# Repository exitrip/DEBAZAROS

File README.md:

<p align="center">
  
  <br>
  <sub>Robert Fludd, <i>Utriusque Cosmi Maioris … Historia</i> (1617)</sub>
</p>

> [!IMPORTANT]
> This repo contains a lot of LLM generated code as of about Aug. 15th 2026.  
> Generally this is bad for the world as much as I wanna hem and haw about
> recycling all the embodied energy in this hardware, but it's also been really
> good for the maturity of this project and my own sanity as professionally 
> overwhelmed engineer.  Most of the important  parts of the design, the core 
> block diagram, hardware, and ring-modulated colour matrix mixer predate my 
> summoning with and bargaining with the **F**ascist **A**hrimanic **D**istributed 
> paywalled coding machine.  "AI" (I'm still linquistically miffed that they managed to
> steal this term) is functionally just a paywall.  "AI" as a term is being used as a dissonant 
> basket for many unrelated systems, and it seems the common factor is the paywall...
> pay for matrix multiplier hardware machine time and pay for stolen goods.  That said, 
> these systems can generate and test a month's of VDHL, C, **AND** javascript in an afternoon.
> One day this will all be obsolete too.

# DEBAZAROS

DEBAZAROS is a video playback and video-feedback unit. It is made from an
EBAZ4205 board, the control board of a discarded crypto-mining machine, plus a
small adapter PCB with three HDMI connectors. These boards are thrown away by
the thousand, but each one has a Zynq-7010 (two ARM cores and an FPGA) and
256 MB of DDR3. This project puts that hardware to full use, as an
installation of many units on one network.

One unit:

- plays movies or generated images on **two HDMI/DVI outputs**;
- **captures a third HDMI/DVI input** live into memory;
- mixes the two outputs into each other in the FPGA (**video feedback**), with
  gain stages, a per-pixel 3×3 colour matrix, a colour key, and two
  oscillators (DDS pattern engines with a sequencer and a drawn waveform);
- sends and receives **HDMI audio** (48 kHz stereo), with an ALSA sound card;
- reacts to sound: an FFT of the input audio drives any control;
- is controlled over the network with **OSC** (Open Sound Control), from a
  web app on the unit, and from cues (scenes and shows) stored on the unit;
- has six buttons, a 6-line GPIO header and two 12 V fan connectors as I/O.

> Status (Nov 2026): the 2-out/1-in design with HDMI audio works on the
> bench board at 720p60. The software runs on the board (web app, cues,
> datamosh, video wall, audio reactivity). Next: the SD card image with the
> software built in (PetaLinux recipe `debaz-sw`) and the fleet. See
> [ROADMAP.md](ROADMAP.md).

This repository started as a fork of Guido's
[EBAZ4205 SDR and Spectrum](https://github.com/guido57/EBAZ4205_Spectrum)
project. The radio parts are no longer used; see "Legacy folders" below.

## Hardware

| Part | Notes |
| --- | --- |
| EBAZ4205 | Zynq XC7Z010-1CLG400, 256 MB DDR3, ethernet, SD card. The ethernet PHY gets its 25 MHz clock from the FPGA, so every bitstream must keep that clock. |
| Adapter PCB `pcb/3xHDMI` (rev v2) | Power, three HDMI connectors on the EBAZ DATA1–3 headers, six buttons, header P1 (6 GPIO + 3V3 + GND). KiCad project and a JLCPCB release are in the folder. |
| Ports | HDMI_0 and HDMI_1 are outputs (DVI or HDMI with audio). HDMI_2 is an input (EDID: 720p60, 1080p30, 1280x960@60, 1280x1024@60, 1600x1200@30; 48 kHz stereo audio). |

The signals are TMDS at 3.3 V from the FPGA pins (DVI levels). Most HDMI
monitors accept them.

## How it works

![Signal flow: the modulated channel (frame buffer 0 through a 9-channel matrix modulator with keying, pixel delay, sine and sawtooth oscillators) drives output 0; the summed channel (frame buffer 1, oscillator layers and feedback from output 0, each with a per-colour gain) drives output 1; the HDMI input passes through to frame buffer 2](debazaros-signalflow.jpg)

| Diagram | Block design / software |
| --- | --- |
| Modulated channel → DVI/HDMI #0 output | `HDMI_0`: `mixerMatrix` (`/mixer/0..8/...`), `colorGainMain` (`/hdmi/0/gain`) |
| Matrix modulator #0–#8 | the 9 mixer channels; the keying modes are mode `0x10`–`0x13` and `0x20`–`0x23` |
| Pixel buffer / pixel delay | BRAM line delay = mixer stream B (`/hdmi/0/delay`) |
| Summed channel → DVI/HDMI #1 output | `HDMI_1`: `/hdmi/1/gain`, `/hdmi/1/osc/sin/...`, `/hdmi/1/osc/phase/...` |
| Feedback per-colour gain | `/hdmi/1/feedback` (output 0 into output 1) |
| Pass-through channel, DVI/HDMI #3 input | `HDMI_2` capture into DDR (`/disp/<d>/capture` shows it) |

The same data from the memory side:

```text
                 DDR3 frame slots (0x0800_0000, 6 slots of 1920x1080x4)
                   │ slot 0 = /dev/fb0             ▲ slot 4 = live input
                   ▼                                │
  ffmpeg ─► fbfeed ─►  VDMA ─► HDMI_0 effects ──┬──► TMDS out 0
  (or drawing)          │      (colour matrix,   │
                        │       mixer, DDS)  ◄───┼─── cross-feed
                        ▼                        │
                       VDMA ─► HDMI_1 effects ◄──┘──► TMDS out 1
                               (feedback gains,
                                oscillator layers)
  HDMI_2 in ─► dvi2rgb ─► vid_in ─► VDMA (write) ─► slot 4
```

- **PS (ARM, Linux):** PetaLinux 2022.2. Programs write frames into reserved
  DDR memory ("slots"). Each display shows one slot. The daemon `debazd` owns
  the FPGA control registers and the slot routing.
- **PL (FPGA):** each output runs a VDMA, a timing generator (shared), an
  effects chain, and an HDMI/DVI encoder with audio (`hw/rtl/hdmi_tx`). The two outputs feed each other's final
  pixels back in: that loop makes the video feedback. The input path decodes
  DVI and writes frames to DDR.
- **Control:** OSC over UDP, port 9000. Every control register has a name, for
  example `/hdmi/1/feedback/rgb` or `/mixer/3/mode`.

## Repository map

| Path | What it is |
| --- | --- |
| [`hw/`](hw/README.md) | Gateware as Tcl. `hw/bd/<variant>.tcl` is the source of the block design. `hw/build.tcl` makes the Vivado project, the bitstream, the XSA and `hw_map.h`. |
| [`sw/`](sw/README.md) | All software for the board: `debazd` (control daemon), `dzctl` (OSC client), `dzweb` (web app), `hdmi2` (display bring-up), `fbfeed` (frames from a pipe into a slot), `libdz`. Plain `make`, no Vitis project. |
| [`artifacts/`](artifacts/README.md) | Bitstreams and XSA in use (hardware-tested builds only). |
| `ip_repo/`, `IP_dvi2rgb/`, `IP_rgb2dvi/`, `IP_axi_dynclk/` | Custom and Digilent IP cores used by the block design. |
| [`PetaLinux/`](PetaLinux) | PetaLinux configuration (the build machine is separate). The one device tree source is `PetaLinux/project-spec/meta-user/recipes-bsp/device-tree/files/system-user.dtsi`; `PetaLinux/dtb/` has the DTB now on the bench board. |
| `debazarosit.sh`, `debazit.service` | Old start script of the first installation (replaced by `sw/tools/dzstart.sh` and the image's `debaz.service`; kept for reference). |
| `pcb/3xHDMI/` | Adapter PCB (KiCad). `pcb/3xHDMIv1/` is the first revision. |
| [ROADMAP.md](ROADMAP.md) | Plan, status and open questions. |
| [CLAUDE.md](CLAUDE.md) | Detailed engineering notes: address map, register fields, measured problems and their causes. |

The original hand-made Vivado project, the Vitis workspace and the folders of
the radio project that this repository started from were removed on
2026-10-25. They are in the branch `legacy-vivado-project`.

## Getting started

You need:

- Vivado 2022.2 (for the gateware, and its Vitis gcc for the ARM software);
- PetaLinux 2022.2 on an Ubuntu 22.04 computer for the SD card image
  ([PetaLinux/README.md](PetaLinux/README.md));
- for development: the board on the LAN (user `ebaz`, empty password).

### 1. Build the gateware

```sh
vivado -mode batch -source hw/build.tcl -tclargs ebaz4205_2out1in build
# -> build/ebaz4205_2out1in/*.bit, *.bit.bin, *.xsa, hw_map.h
```

See [hw/README.md](hw/README.md) for the edit cycle in the Vivado GUI.
Hardware-tested builds go to [artifacts/](artifacts/README.md).

### 2. The SD card image

The image (PetaLinux) holds BOOT.BIN with the current bitstream, Linux, and
the software from `sw/` (recipe `debaz-sw`). At boot `debaz.service` starts
the displays, the control daemon and the web app. Flash it, power up, open
`http://<unit-ip>:8080/`. Build: [PetaLinux/README.md](PetaLinux/README.md).

### 3. Development: build and install the software

```sh
make -C sw                                  # ARM binaries in sw/out/arm/
make -C sw test                             # host self test, no hardware needed
make -C sw install TARGET=ebaz@<unit-ip>    # copy to /home/ebaz/bin, /home/ebaz/www
```

The copy in `/home/ebaz` wins over the image's `/usr/bin` (see
[sw/README.md](sw/README.md)). Restart it on the board:
`sudo sh /home/ebaz/bin/dzstart.sh` (with a PL load when
`/home/ebaz/dzstart.conf` names a bitstream).

### 4. Control it

```sh
dzctl -s                                    # find all units on the network
dzctl -h <ip> /list                         # all control addresses
dzctl -h <ip> /hdmi/1/feedback/rgb 200 40 40
dzctl -h <ip> /disp/0/capture               # show the live input on display 0
dzctl -h <ip> /movie/0/file test24.mp4      # play a movie into slot 0
dzctl -h <ip> /video/mode 800x600           # output mode of both displays
dzctl -h <ip> /cue/go scene1 1 2 fade       # a cue, with a 2 s fade
```

Any OSC program can send the same messages to UDP port 9000. The web app
uses the same addresses (hover a control to see its message).

## Important cautions

- **Frame memory must be reserved.** The video hardware writes DDR directly.
  If the reserved region is too small, it overwrites Linux memory and programs
  crash. The image's device tree reserves 96 MB; 128 MB does not work with
  this U-Boot (the kernel rejects it). Check the hole in `/proc/iomem`.
- **Do not reload the FPGA while the input capture runs.** Stop the capture
  first. If you do not, the capture can stay dead until a power cycle.
- **FCLK3 must be 200 MHz** for the input. The FSBL of the PetaLinux image
  sets it; old cards (Jan 2025 image) set 25 MHz and need the SLCR poke in
  CLAUDE.md after each boot.
- **Software and bitstream belong together.** `sw/include/hw_map.h` follows
  one block design; debazd on an older bitstream can hit removed addresses.
  The image ships matching pairs; for development, `dzstart.conf` names the
  bitstream to load.
- **Mixer after a power-up:** HDMI_0's output stays black until the mixer is
  set up. `dzstart.sh` (at boot) and `plreload.sh` run `dzsetup.sh` for it.
- Every board starts with the same MAC address (`00:0a:35:00:1e:53`; the
  factory MAC in the NAND is the same on every board too). The image's first
  boot gives each card its own MAC from the SD card CID (`debaz-mac.sh`, one
  extra reboot); old cards: `sudo sh debaz-mac.sh -w -r`.

## Credits and license

- Original EBAZ4205 work: Guido ([guido57](https://github.com/guido57)),
  EBAZ4205 SDR and Spectrum.
- DVI IP cores (`dvi2rgb`, `rgb2dvi`, `axi_dynclk`) and the TMDS interface
  definition: [Digilent vivado-library](https://github.com/Digilent/vivado-library), MIT.
- Xilinx IP cores are under their own licenses.

This project: MIT.

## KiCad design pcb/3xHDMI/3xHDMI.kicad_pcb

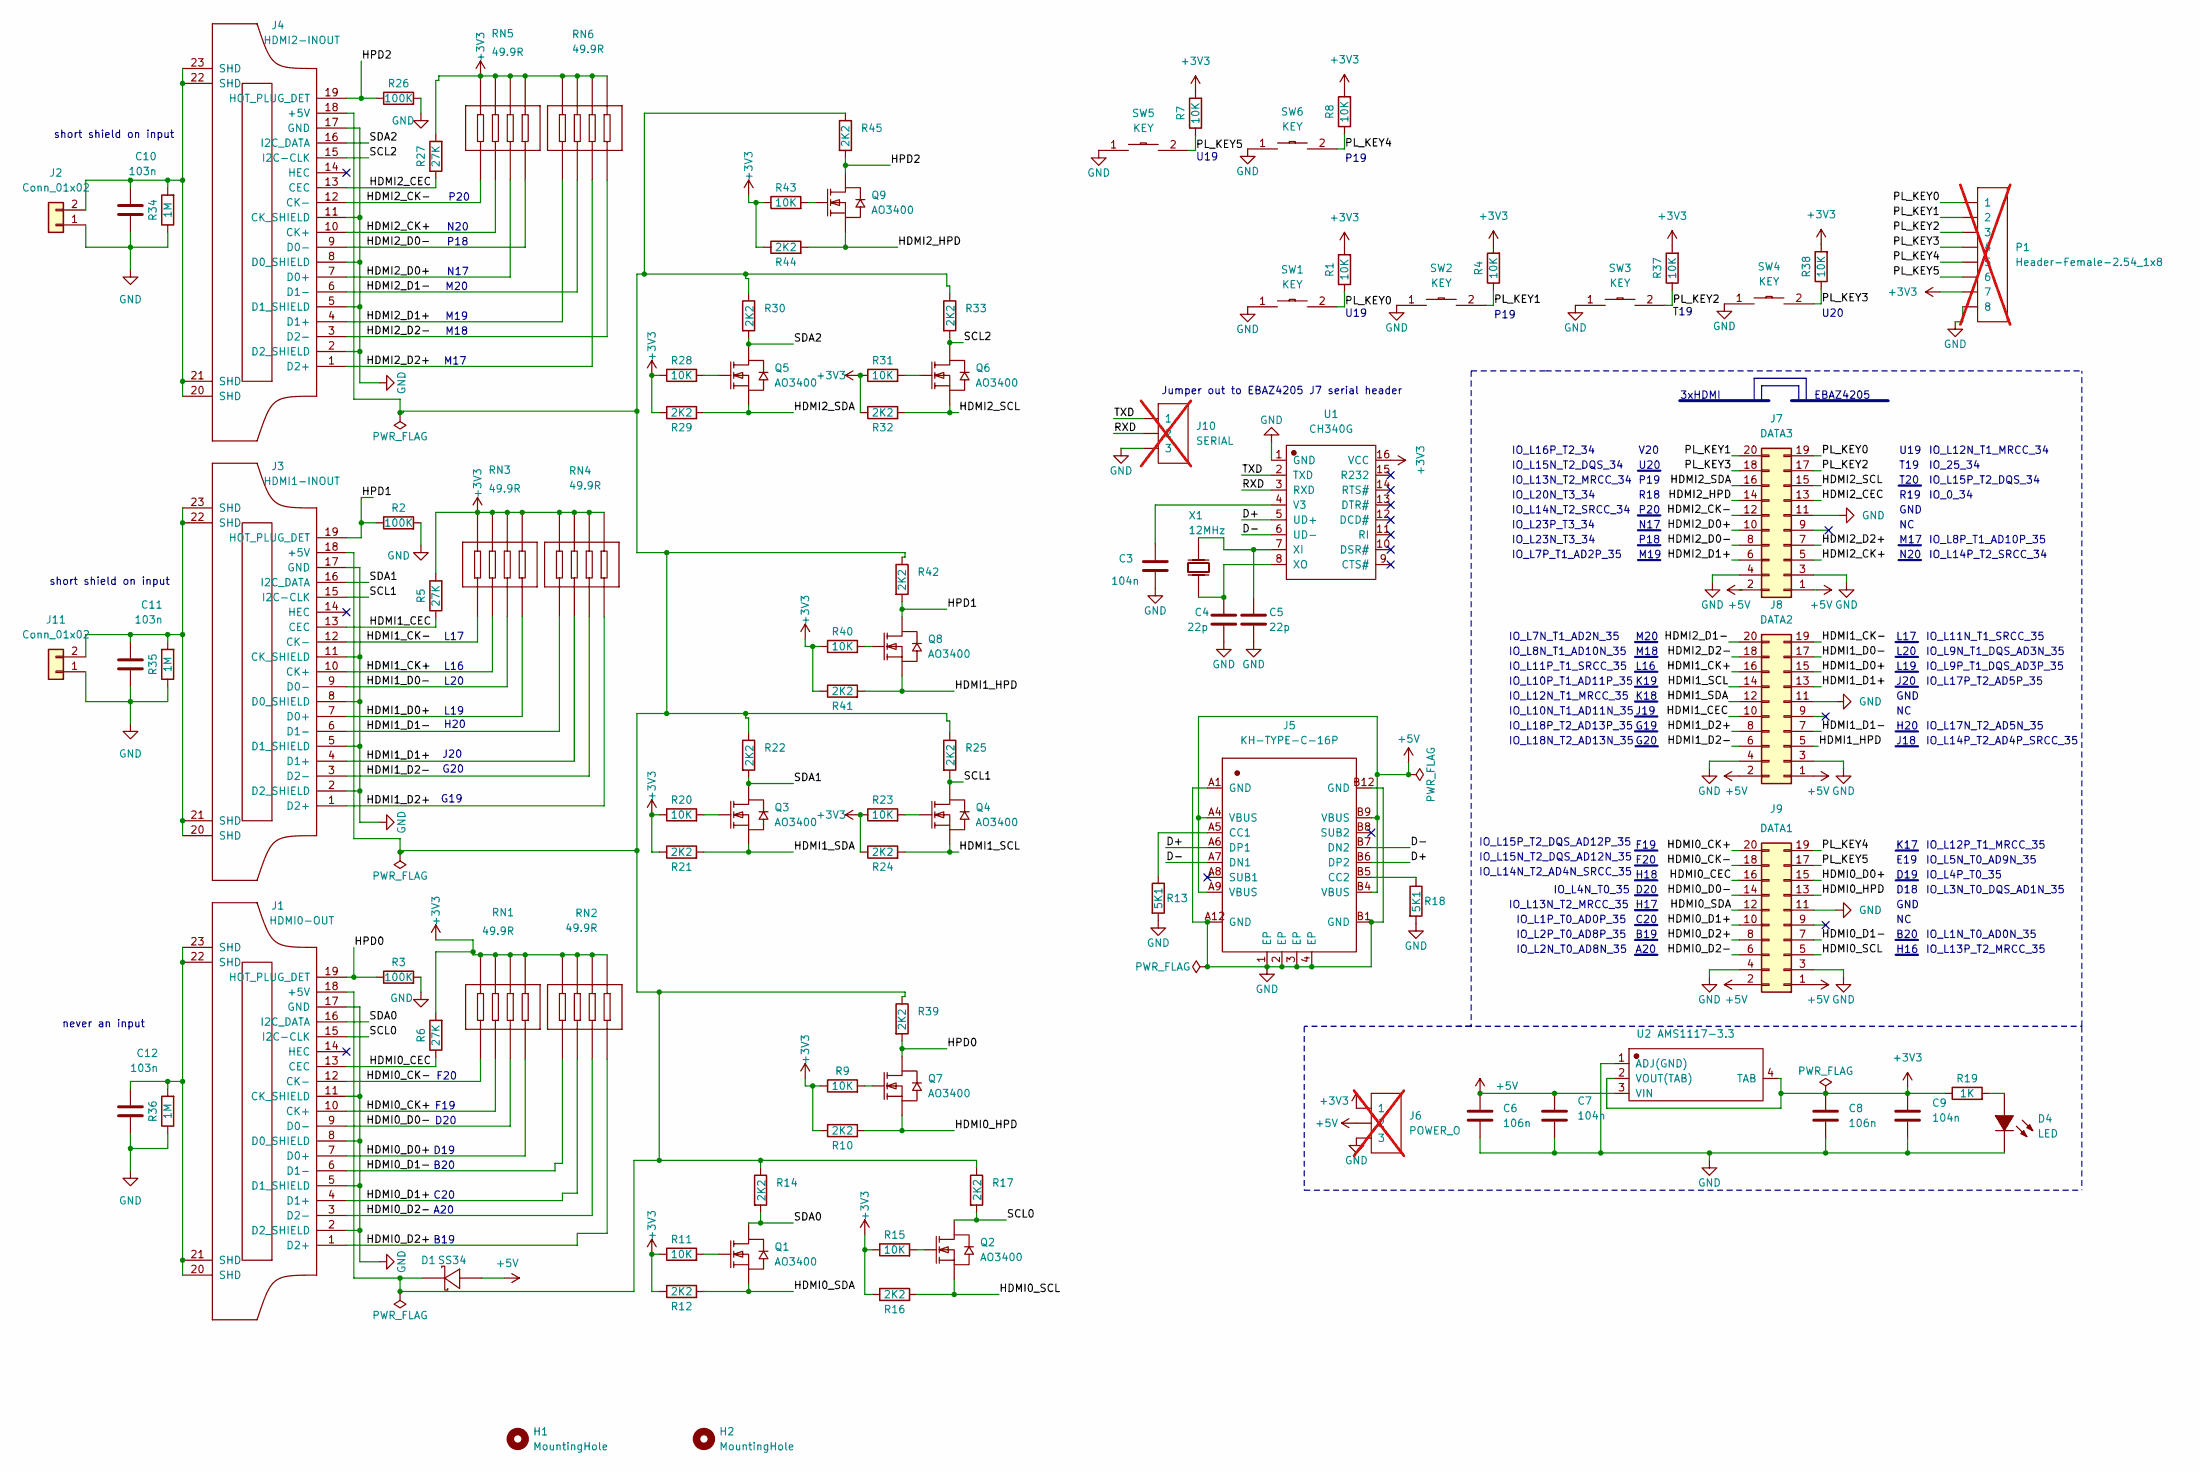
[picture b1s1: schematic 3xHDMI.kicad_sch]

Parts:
C3, C7, C9: 104n; C0603
C4, C5: 22p; C0603
C6, C8: 106n; C0603
C10, C11, C12: 103n; C0603
D1: SS34; DO-214AC_L4.3-W2.7-LS5.3-RD
D4: LED; LED0603-FD
H1, H2: MountingHole; MountingHole_3.2mm_M3
J1: HDMI0-OUT; HDMI-SMD_HDMI-019S
J2, J11: Conn_01x02; PinHeader_1x02_P2.54mm_Vertical_SMD_Pin1Left
J3: HDMI1-INOUT; HDMI-SMD_HDMI-019S
J4: HDMI2-INOUT; HDMI-SMD_HDMI-019S
J5: KH-TYPE-C-16P; USB-C-SMD_KH-TYPE-C-16P
J6: POWER_O; HDR-TH_3P-P2.54-V-M-1; not fitted
J7: DATA3; EBAZEXT-DAT
J8: DATA2; EBAZEXT-DAT
J9: DATA1; EBAZEXT-DAT
J10: SERIAL; HDR-TH_3P-P2.54-V-M-1; not fitted
P1: Header-Female-2.54_1x8; HDR-TH_8P-P2.54-V-F-1; not fitted
Q1, Q2, Q3, Q4, Q5, Q6, Q7, Q8, Q9: AO3400; SOT-23_L2.9-W1.3-P1.90-LS2.4-BR
R1, R4, R7, R8, R9, R11, R15, R20, R23, R28, R31, R37, R38, R40, R43: 10K; R0603
R2, R3, R26: 100K; R0603
R5, R6, R27: 27K; R0603
R10, R12, R14, R16, R17, R21, R22, R24, R25, R29, R30, R32, R33, R39, R41, R42, R44, R45: 2K2; R0603
R13, R18: 5K1; R0603
R19: 1K; R0603
R34, R35, R36: 1M; R0603
RN1, RN2, RN3, RN4, RN5, RN6: 49.9R; RES-ARRAY-SMD_0603-8P-L3.2-W1.6-BL
SW1, SW2, SW3, SW4, SW5, SW6: KEY; SW-SMD_L6.0-W3.3-LS8.0
U1: CH340G; SOIC-16_L9.9-W3.9-P1.27-LS6.0-BL
U2: AMS1117-3.3; SOT-223-4_L6.5-W3.5-P2.30-LS7.0-BR
X1: 12MHz; HC-49S_L11.4-W4.8

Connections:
+3V3: C8.1, C9.1, J6.1, P1.7, R1.2, R4.2, R5.2, R6.2, R7.2, R8.2, R9.1, R10.1, R11.1, R12.1, R15.1, R16.1, R19.1, R20.1, R21.1, R23.1, R24.1, R27.2, R28.1, R29.1, R31.1, R32.1, R37.2, R38.2, R40.1, R41.1, R43.1, R44.1, RN1.5, RN1.6, RN1.7, RN1.8, RN2.5, RN2.6, RN2.7, RN2.8, RN3.5, RN3.6, RN3.7, RN3.8, RN4.5, RN4.6, RN4.7, RN4.8, RN5.5, RN5.6, RN5.7, RN5.8, RN6.5, RN6.6, RN6.7, RN6.8, U1.16 (VCC), U2.2 (VOUT(TAB)), U2.4 (TAB)
+5V: C6.1, C7.1, D1.2 (A), J5.A4 (VBUS), J5.A9 (VBUS), J5.B4 (VBUS), J5.B9 (VBUS), J6.2, J7.1, J7.2, J8.1, J8.2, J9.1, J9.2, U2.3 (VIN)
/D+: J5.A6 (DP1), J5.B6 (DP2), U1.5 (UD+)
/D-: J5.A7 (DN1), J5.B7 (DN2), U1.6 (UD-)
/HDMI0_CEC: J1.13 (CEC), J9.16, R6.1
/HDMI0_CK+: J1.10 (CK+), J9.20, RN1.3
/HDMI0_CK-: J1.12 (CK-), J9.18, RN1.4
/HDMI0_D0+: J1.7 (D0+), J9.15, RN1.1
/HDMI0_D0-: J1.9 (D0-), J9.14, RN1.2
/HDMI0_D1+: J1.4 (D1+), J9.10, RN2.3
/HDMI0_D1-: J1.6 (D1-), J9.7, RN2.4
/HDMI0_D2+: J1.1 (D2+), J9.8, RN2.1
/HDMI0_D2-: J1.3 (D2-), J9.6, RN2.2
/HDMI0_HPD: J9.13, Q7.2 (S), R10.2
/HDMI0_SCL: J9.5, Q2.2 (S), R16.2
/HDMI0_SDA: J9.12, Q1.2 (S), R12.2
/HDMI1_CEC: J3.13 (CEC), J8.10, R5.1
/HDMI1_CK+: J3.10 (CK+), J8.16, RN3.2
/HDMI1_CK-: J3.12 (CK-), J8.19, RN3.1
/HDMI1_D0+: J3.7 (D0+), J8.15, RN3.4
/HDMI1_D0-: J3.9 (D0-), J8.17, RN3.3
/HDMI1_D1+: J3.4 (D1+), J8.13, RN4.2
/HDMI1_D1-: J3.6 (D1-), J8.7, RN4.1
/HDMI1_D2+: J3.1 (D2+), J8.8, RN4.4
/HDMI1_D2-: J3.3 (D2-), J8.6, RN4.3
/HDMI1_HPD: J8.5, Q8.2 (S), R41.2
/HDMI1_SCL: J8.14, Q4.2 (S), R24.2
/HDMI1_SDA: J8.12, Q3.2 (S), R21.2
/HDMI2_CEC: J4.13 (CEC), J7.13, R27.1
/HDMI2_CK+: J4.10 (CK+), J7.5, RN5.2
/HDMI2_CK-: J4.12 (CK-), J7.12, RN5.1
/HDMI2_D0+: J4.7 (D0+), J7.10, RN5.3
/HDMI2_D0-: J4.9 (D0-), J7.8, RN5.4
/HDMI2_D1+: J4.4 (D1+), J7.6, RN6.1
/HDMI2_D1-: J4.6 (D1-), J8.20, RN6.2
/HDMI2_D2+: J4.1 (D2+), J7.7, RN6.3
/HDMI2_D2-: J4.3 (D2-), J8.18, RN6.4
/HDMI2_HPD: J7.14, Q9.2 (S), R44.2
/HDMI2_SCL: J7.15, Q6.2 (S), R32.2
/HDMI2_SDA: J7.16, Q5.2 (S), R29.2
/HPD0: J1.19 (HOT_PLUG_DET), Q7.3 (D), R3.1, R39.2
/HPD1: J3.19 (HOT_PLUG_DET), Q8.3 (D), R2.1, R42.2
/HPD2: J4.19 (HOT_PLUG_DET), Q9.3 (D), R26.1, R45.2
/PL_KEY0: J7.19, P1.1, R1.1, SW1.2
/PL_KEY1: J7.20, P1.2, R4.1, SW2.2
/PL_KEY2: J7.17, P1.3, R37.1, SW3.2
/PL_KEY3: J7.18, P1.4, R38.1, SW4.2
/PL_KEY4: J9.19, P1.5, R8.1, SW6.2
/PL_KEY5: J9.17, P1.6, R7.1, SW5.2
/RXD: J10.2, U1.3 (RXD)
/SCL0: J1.15 (I2C-CLK), Q2.3 (D), R17.2
/SCL1: J3.15 (I2C-CLK), Q4.3 (D), R25.2
/SCL2: J4.15 (I2C-CLK), Q6.3 (D), R33.2
/SDA0: J1.16 (I2C_DATA), Q1.3 (D), R14.2
/SDA1: J3.16 (I2C_DATA), Q3.3 (D), R22.2
/SDA2: J4.16 (I2C_DATA), Q5.3 (D), R30.2
/TXD: J10.1, U1.2 (TXD)
GND: C3.2, C4.2, C5.2, C6.2, C7.2, C8.2, C9.2, C10.2, C11.2, C12.2, D4.2 (K), J1.2 (D2_SHIELD), J1.5 (D1_SHIELD), J1.8 (D0_SHIELD), J1.11 (CK_SHIELD), J1.17 (GND), J2.1, J3.2 (D2_SHIELD), J3.5 (D1_SHIELD), J3.8 (D0_SHIELD), J3.11 (CK_SHIELD), J3.17 (GND), J4.2 (D2_SHIELD), J4.5 (D1_SHIELD), J4.8 (D0_SHIELD), J4.11 (CK_SHIELD), J4.17 (GND), J5.1 (EP), J5.2 (EP), J5.3 (EP), J5.4 (EP), J5.A1 (GND), J5.A12 (GND), J5.B1 (GND), J5.B12 (GND), J6.3, J7.3, J7.4, J7.11, J8.3, J8.4, J8.11, J9.3, J9.4, J9.11, J10.3, J11.1, P1.8, R2.2, R3.2, R13.2, R18.2, R26.2, R34.1, R35.1, R36.1, SW1.1, SW2.1, SW3.1, SW4.1, SW5.1, SW6.1, U1.1 (GND), U2.1 (ADJ(GND))
unnamed: C12.1, J1.20 (SHD), J1.21 (SHD), J1.22 (SHD), J1.23 (SHD), R36.2
unnamed: D1.1 (K), J1.18 (+5V), J3.18 (+5V), J4.18 (+5V), R14.1, R17.1, R22.1, R25.1, R30.1, R33.1, R39.1, R42.1, R45.1
unnamed: D4.1 (A), R19.2
unnamed: C10.1, J2.2, J4.20 (SHD), J4.21 (SHD), J4.22 (SHD), J4.23 (SHD), R34.2
unnamed: J5.A5 (CC1), R13.1
unnamed: J5.B5 (CC2), R18.1
unnamed: C11.1, J3.20 (SHD), J3.21 (SHD), J3.22 (SHD), J3.23 (SHD), J11.2, R35.2
unnamed: Q1.1 (G), R11.2
unnamed: Q2.1 (G), R15.2
unnamed: Q3.1 (G), R20.2
unnamed: Q4.1 (G), R23.2
unnamed: Q5.1 (G), R28.2
unnamed: Q6.1 (G), R31.2
unnamed: Q7.1 (G), R9.2
unnamed: Q8.1 (G), R40.2
unnamed: Q9.1 (G), R43.2
unnamed: C3.1, U1.4 (V3)
unnamed: C5.1, U1.7 (XI), X1.1 (OSC1)
unnamed: C4.1, U1.8 (XO), X1.2 (OSC2)

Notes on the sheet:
IO_L3N_T0_DQS_AD1N_35
EBAZ4205
B19
M20
G20
L19
C20
IO_L11N_T1_SRCC_35
P19
GND
IO_L10P_T1_AD11P_35
IO_L5N_T0_AD9N_35
F20
IO_L9N_T1_DQS_AD3N_35
J18
K19
IO_L13P_T2_MRCC_35
R18
IO_L13N_T2_MRCC_35
A20
F19
IO_L9P_T1_DQS_AD3P_35
N20
IO_L1N_T0_AD0N_35
N17
L20
P20
G19
IO_L15P_T2_DQS_AD12P_35
D20
IO_L2P_T0_AD8P_35
IO_25_34
H20
short shield on input
IO_L23N_T3_34
3xHDMI
IO_L14N_T2_AD4N_SRCC_35
M18
H17
never an input

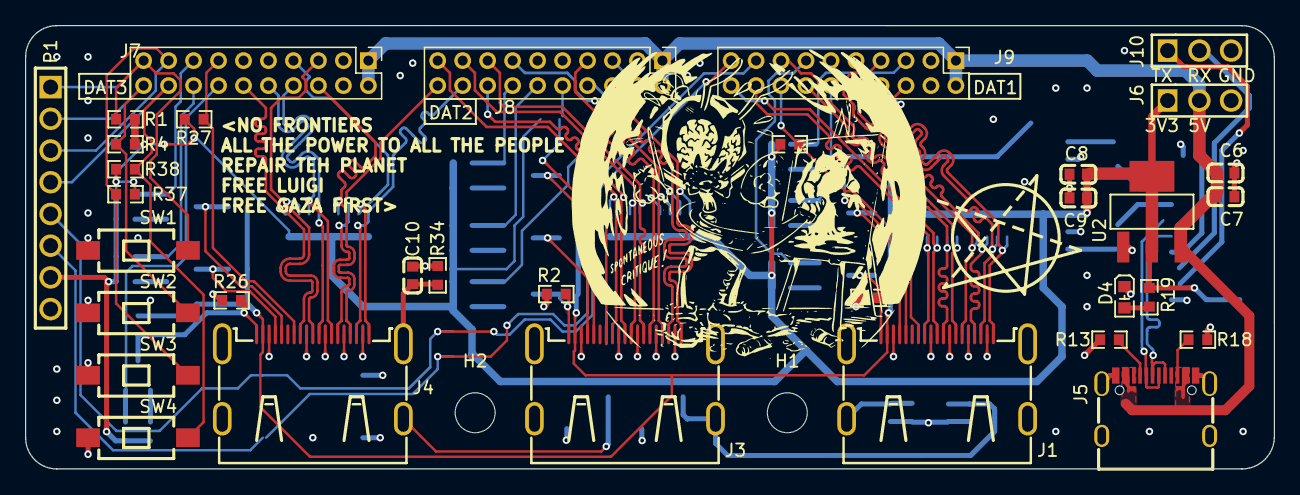
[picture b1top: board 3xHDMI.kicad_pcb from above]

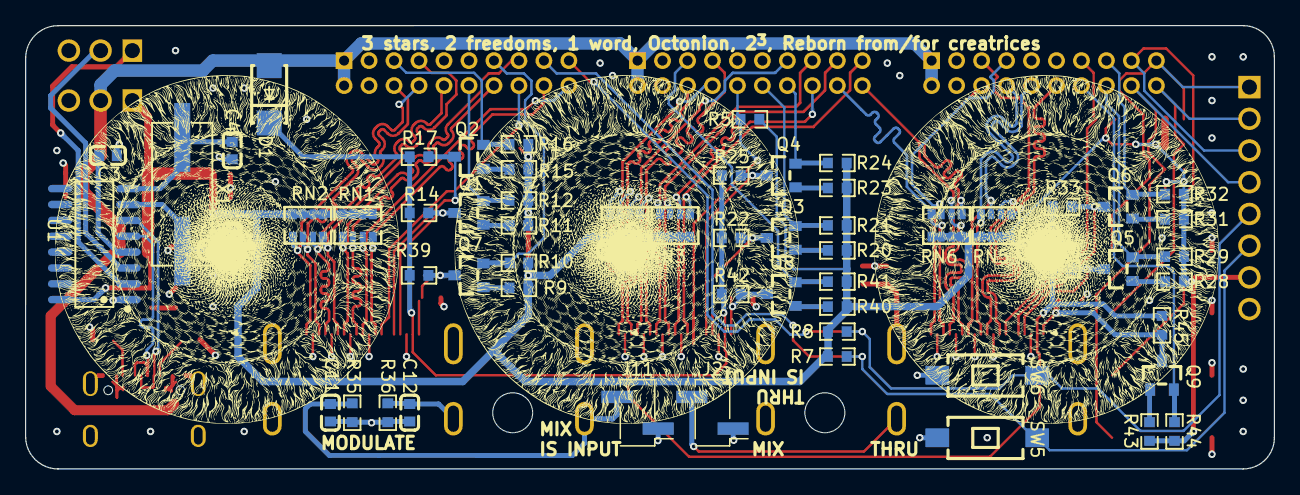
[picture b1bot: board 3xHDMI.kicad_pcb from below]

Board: 4 copper layers, 100.0 x 35.5 mm, 95 parts (59 on the bottom side), 77 nets.

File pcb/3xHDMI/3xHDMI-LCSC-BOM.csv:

#,Reference,Value,Qty,SuppliersPartNumber
1,"C3,C7,C9",104n,3,C14663
2,"C4,C5",22p,2,C1653
3,"C6,C8",106n,2,C19702
4,"C10,C11,C12",103n,3,C57112
5,D1,SS34,1,C8678
6,D4,LED,1,C84263
7,J1,HDMI0-OUT,1,C111617
9,J3,HDMI1-INOUT,1,C111617
10,J4,HDMI2-INOUT,1,C111617
11,J5,KH-TYPE-C-16P,1,C709357
12,J6,POWER_O,1,C49257
13,J7,DATA3,1,C3012193
14,J8,DATA2,1,C3012193
15,J9,DATA1,1,C3012193
16,J10,SERIAL,1,C49257
17,P1,Header-Female-2.54_1x8,1,C27438
18,"Q1,Q2,Q3,Q4,Q5,Q6,Q7,Q8,Q9",AO3400,9,C344010
19,"R1,R4,R7,R8,R9,R11,R15,R20,R23,R28,R31,R37,R38,R40,R43",10K,15,C25804
20,"R2,R3,R26",100K,3,C25803
21,"R5,R6,R27",27K,3,C22967
22,"R10,R12,R14,R16,R17,R21,R22,R24,R25,R29,R30,R32,R33,R39,R41,R42,R44,R45",2K2,18,C4190
23,"R13,R18",5K1,2,C23186
24,R19,1K,1,C21190
25,"R34,R35,R36",1M,3,C22935
26,"RN1,RN2,RN3,RN4,RN5,RN6",49.9R,6,C54832
27,"SW1,SW2,SW3,SW4,SW5,SW6",KEY,6,C318938
28,U1,CH340G,1,C14267
29,U2,AMS1117-3.3,1,C347222
30,X1,12MHz,1,C14871

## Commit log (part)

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2024-10-26 building with extBrd HDMI pinout... not having these sources tracked really effed up the other branches
2024-10-26 removed SDR circuits but kept audio i/o
2024-10-26 pull dynclk out of HDMI block to get ready to global buff the pixel clk
2024-10-27 clean up vivado proj
2024-10-31 branching bd with 2 outs
2024-10-31 bitstream builds
2024-11-07 save mixer work on new branch
2024-11-08 mid edit of v1.1 mixer...
2024-12-10 god test this mess
2024-12-11 mixer signal chain does trash anymoregit status! also theres's feedback loop between hdmiAught y einz
2024-12-12 add tcl export, not tested...
2024-12-12 i think... this works... just remember to turn incremental alll the way off before write_project_tcling
2024-12-12 oooooffffff
2024-12-15 :ctrl-s
2025-01-26 ugh... should just ignore everything in .src
2025-01-26 add r1 pcb
2025-01-26 update with 3x pcb pinout, but only 0 and 1 are enabled.... yet to re-wade into previously failed clock distro experiments
2025-01-27 tested twerking
2025-02-22 tryna figure out this clk shit
2025-02-23 Revert "tryna figure out this clk shit"
    This reverts commit ad6a9c738b1ba4c81765aa10b25effe9aea2352e.
2025-02-23 fix hdmi1 clk pinout
2025-02-23 works okay
2025-02-23 nuMixer tests ok with 1 channel
2025-09-08 still no green on output1
2025-09-08 better nuMixer, now with GREEN
2025-09-09 clipping not working
2025-09-11 test osciallator on hdmi1 and got clipping and colors almost sorted
2025-09-12 basic feed back loop works!!! not surprising its touchy... only usable with pixclk below 720p@30Hz / 35MHZ
2025-09-17 simple mixers for hdmi1 working!
2025-12-29 save dtsi
2026-01-01 add rgb2dvi IP folder outside of vivado
2026-01-01 recovered a decent build... after braking trying out frame buffer read IP
